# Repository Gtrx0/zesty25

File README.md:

# Zesty 25
5x5 Macropad PCB

# [Layout](http://www.keyboard-layout-editor.com/#/gists/2997f919e892d07fd131f2b731a871e9)

## Features
* In-switch LED support.
* Individually addressible RGB underglow provided by 4 separate WS2812B LEDs.
* Compatible with Cherry MX and ALPS switches.
* Pro Micro microcontroller for easy diy assembly.
* THT diodes and resistors for diy assembly.

## Warning
KiCad 5 or above is needed to open this project. KiCad 4 or below won't work.

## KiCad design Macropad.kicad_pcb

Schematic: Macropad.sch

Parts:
CR1, CR2, CR3, CR4: 0.1u; C_0805_HandSoldering
D1, D2, D3, D4, D5, D6, D7, D8, D9, D10, D11, D12, D13, D14, D15, D16, D17, D18, D19, D20, D21, D22, D23, D24, D25: DIODE
K1: KEYSW; rstgg
MX1, MX2, MX3, MX4, MX5, MX6, MX7, MX8, MX9, MX10, MX11, MX12, MX13, MX14, MX15, MX16, MX17, MX18, MX19, MX20, MX21, MX22, MX23, MX24, MX25: MX-1.25U; MX-1U
NPNR1: 1.5k; R_Axial_DIN0204_L3.6mm_D1.6mm_P7.62mm_Horizontal
Q1: Q_NPN_BCE; SOT-223-3_TabPin2
R1: R1; R_Axial_DIN0204_L3.6mm_D1.6mm_P7.62mm_Horizontal
R2: R2; R_Axial_DIN0204_L3.6mm_D1.6mm_P7.62mm_Horizontal
R3: R3; R_Axial_DIN0204_L3.6mm_D1.6mm_P7.62mm_Horizontal
R4: R4; R_Axial_DIN0204_L3.6mm_D1.6mm_P7.62mm_Horizontal
R5: R5; R_Axial_DIN0204_L3.6mm_D1.6mm_P7.62mm_Horizontal
R6: R6; R_Axial_DIN0204_L3.6mm_D1.6mm_P7.62mm_Horizontal
R7: R7; R_Axial_DIN0204_L3.6mm_D1.6mm_P7.62mm_Horizontal
R8: R8; R_Axial_DIN0204_L3.6mm_D1.6mm_P7.62mm_Horizontal
R9: R9; R_Axial_DIN0204_L3.6mm_D1.6mm_P7.62mm_Horizontal
R10: R10; R_Axial_DIN0204_L3.6mm_D1.6mm_P7.62mm_Horizontal
R11: R11; R_Axial_DIN0204_L3.6mm_D1.6mm_P7.62mm_Horizontal
R12: R12; R_Axial_DIN0204_L3.6mm_D1.6mm_P7.62mm_Horizontal
R13: R13; R_Axial_DIN0204_L3.6mm_D1.6mm_P7.62mm_Horizontal
R14: R14; R_Axial_DIN0204_L3.6mm_D1.6mm_P7.62mm_Horizontal
R15: R15; R_Axial_DIN0204_L3.6mm_D1.6mm_P7.62mm_Horizontal
R16: R16; R_Axial_DIN0204_L3.6mm_D1.6mm_P7.62mm_Horizontal
R17: R17; R_Axial_DIN0204_L3.6mm_D1.6mm_P7.62mm_Horizontal
R18: R18; R_Axial_DIN0204_L3.6mm_D1.6mm_P7.62mm_Horizontal
R19: R19; R_Axial_DIN0204_L3.6mm_D1.6mm_P7.62mm_Horizontal
R20: R20; R_Axial_DIN0204_L3.6mm_D1.6mm_P7.62mm_Horizontal
R21: R_Small; R_Axial_DIN0204_L3.6mm_D1.6mm_P7.62mm_Horizontal
R22: R22; R_Axial_DIN0204_L3.6mm_D1.6mm_P7.62mm_Horizontal
R23: R23; R_Axial_DIN0204_L3.6mm_D1.6mm_P7.62mm_Horizontal
R24: R24; R_Axial_DIN0204_L3.6mm_D1.6mm_P7.62mm_Horizontal
R25: R25; R_Axial_DIN0204_L3.6mm_D1.6mm_P7.62mm_Horizontal
RGB1, RGB2, RGB3, RGB4: WS2812B
RGBR1: 1.5k; R_Axial_DIN0204_L3.6mm_D1.6mm_P7.62mm_Horizontal
U1: ARDUINO_PRO_MICRO; Pro_Micro

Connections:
LEDGND: MX1.4 (LEDGND), MX2.4 (LEDGND), MX3.4 (LEDGND), MX4.4 (LEDGND), MX5.4 (LEDGND), MX6.4 (LEDGND), MX7.4 (LEDGND), MX8.4 (LEDGND), MX9.4 (LEDGND), MX10.4 (LEDGND), MX11.4 (LEDGND), MX12.4 (LEDGND), MX13.4 (LEDGND), MX14.4 (LEDGND), MX15.4 (LEDGND), MX16.4 (LEDGND), MX17.4 (LEDGND), MX18.4 (LEDGND), MX19.4 (LEDGND), MX20.4 (LEDGND), MX21.4 (LEDGND), MX22.4 (LEDGND), MX23.4 (LEDGND), MX24.4 (LEDGND), MX25.4 (LEDGND), Q1.2
LedPwm: U1.12 (9); also elsewhere on the board
unnamed: D1.1 (A), MX1.2 (ROW)
unnamed: D2.1 (A), MX2.2 (ROW)
unnamed: D3.1 (A), MX3.2 (ROW)
unnamed: D4.1 (A), MX4.2 (ROW)
unnamed: D5.1 (A), MX5.2 (ROW)
unnamed: D6.1 (A), MX6.2 (ROW)
unnamed: D7.1 (A), MX7.2 (ROW)
unnamed: D8.1 (A), MX8.2 (ROW)
unnamed: D9.1 (A), MX9.2 (ROW)
unnamed: D10.1 (A), MX10.2 (ROW)
unnamed: D11.1 (A), MX11.2 (ROW)
unnamed: D12.1 (A), MX12.2 (ROW)
unnamed: D13.1 (A), MX13.2 (ROW)
unnamed: D14.1 (A), MX14.2 (ROW)
unnamed: D15.1 (A), MX15.2 (ROW)
unnamed: D16.1 (A), MX16.2 (ROW)
unnamed: D17.1 (A), MX17.2 (ROW)
unnamed: D18.1 (A), MX18.2 (ROW)
unnamed: D19.1 (A), MX19.2 (ROW)
unnamed: D20.1 (A), MX20.2 (ROW)
unnamed: D21.1 (A), MX21.2 (ROW)
unnamed: D22.1 (A), MX22.2 (ROW)
unnamed: D23.1 (A), MX23.2 (ROW)
unnamed: D24.1 (A), MX24.2 (ROW)
unnamed: D25.1 (A), MX25.2 (ROW)
unnamed: MX1.3 (LED), R1.1
unnamed: MX2.3 (LED), R2.1
unnamed: MX3.3 (LED), R3.1
unnamed: MX4.3 (LED), R4.1
unnamed: MX5.3 (LED), R5.1
unnamed: MX6.3 (LED), R6.1
unnamed: MX7.3 (LED), R7.1
unnamed: MX8.3 (LED), R8.1
unnamed: MX9.3 (LED), R9.1
unnamed: MX10.3 (LED), R10.1
unnamed: MX11.3 (LED), R11.1
unnamed: MX12.3 (LED), R12.1
unnamed: MX13.3 (LED), R13.1
unnamed: MX14.3 (LED), R14.1
unnamed: MX15.3 (LED), R15.1
unnamed: MX16.3 (LED), R16.1
unnamed: MX17.3 (LED), R17.1
unnamed: MX18.3 (LED), R18.1
unnamed: MX19.3 (LED), R19.1
unnamed: MX20.3 (LED), R20.1
unnamed: MX21.3 (LED), R21.1
unnamed: MX22.3 (LED), R22.1
unnamed: MX23.3 (LED), R23.1
unnamed: MX24.3 (LED), R24.1
unnamed: MX25.3 (LED), R25.1
unnamed 52: Q1.1; also elsewhere on the board
unnamed: RGB1.2 (DOUT), RGB2.4 (DIN)
unnamed: RGB2.2 (DOUT), RGB3.4 (DIN)
unnamed: RGB3.2 (DOUT), RGB4.4 (DIN)
unnamed 57: U1.9 (6); also elsewhere on the board
RAW: U1.13 (10)
RGBIN: RGB1.4 (DIN); also elsewhere on the board
RST: K1.2, U1.15 (14); also elsewhere on the board
col1: MX1.1 (COL), MX6.1 (COL), MX11.1 (COL), MX16.1 (COL), MX21.1 (COL), U1.22 (RST)
col2: MX2.1 (COL), MX7.1 (COL), MX12.1 (COL), MX17.1 (COL), MX22.1 (COL), U1.23 (GND)
col3: MX3.1 (COL), MX8.1 (COL), MX13.1 (COL), MX18.1 (COL), MX23.1 (COL), U1.5 (2)
col4: MX4.1 (COL), MX9.1 (COL), MX14.1 (COL), MX19.1 (COL), MX24.1 (COL), U1.6 (3)
col5: MX5.1 (COL), MX10.1 (COL), MX15.1 (COL), MX20.1 (COL), MX25.1 (COL), U1.7 (4)
row1: D1.2 (K), D2.2 (K), D3.2 (K), D4.2 (K), D5.2 (K), U1.17 (A0)
row2: D6.2 (K), D7.2 (K), D8.2 (K), D9.2 (K), D10.2 (K), U1.18 (A1)
row3: D11.2 (K), D12.2 (K), D13.2 (K), D14.2 (K), D15.2 (K), U1.19 (A2)
row4: D16.2 (K), D17.2 (K), D18.2 (K), D19.2 (K), D20.2 (K), U1.20 (A3)
row5: D21.2 (K), D22.2 (K), D23.2 (K), D24.2 (K), D25.2 (K), U1.21 (VCC)

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
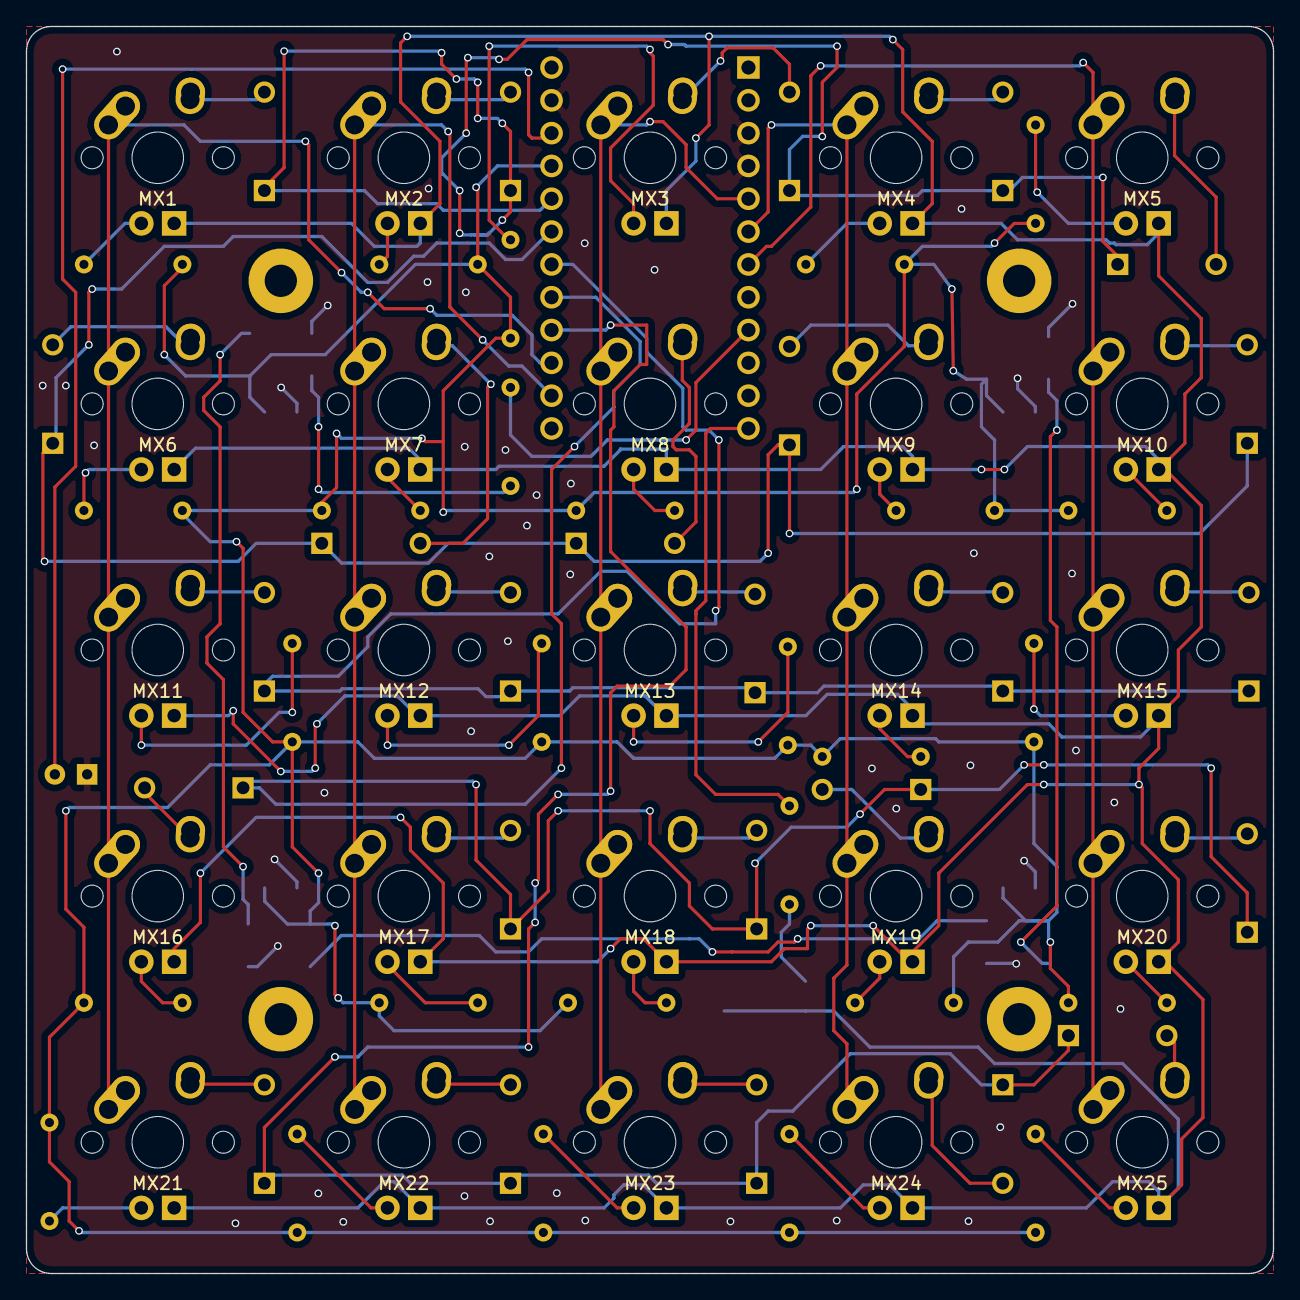
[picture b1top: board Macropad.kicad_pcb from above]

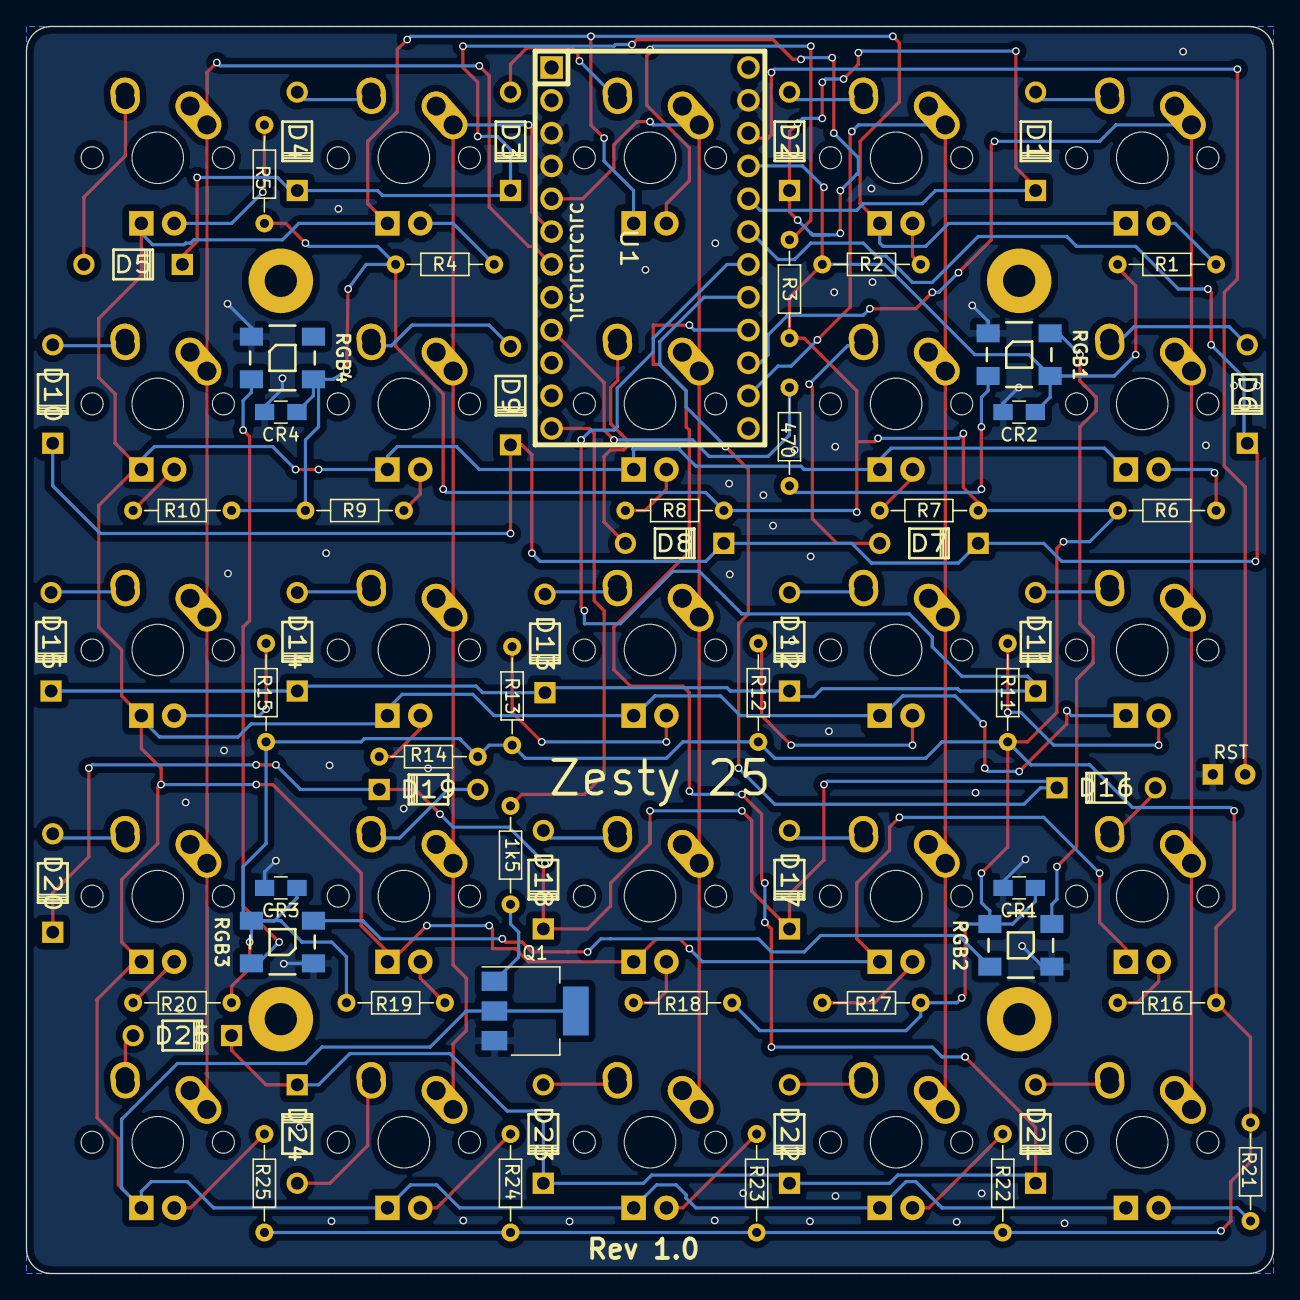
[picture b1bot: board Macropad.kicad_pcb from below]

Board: 2 copper layers, 96.5 x 96.5 mm, 88 parts (63 on the bottom side), 71 nets.

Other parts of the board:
1k5, 470: 1.5k; R_Axial_DIN0204_L3.6mm_D1.6mm_P7.62mm_Horizontal
RST: KEYSW; rstgg

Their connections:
LedPwm: 1k5.2; also elsewhere on the board
unnamed 52: 1k5.1; also elsewhere on the board
unnamed 57: 470.1; also elsewhere on the board
RGBIN: 470.2; also elsewhere on the board
RST: RST.2; also elsewhere on the board

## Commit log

2018-08-24 Zesty25
2018-08-24 License + readme
2018-08-24 Renders
